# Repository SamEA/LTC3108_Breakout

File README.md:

LTC3108_Breakout
================

Energy Harvesting Breakout Board LTC3108

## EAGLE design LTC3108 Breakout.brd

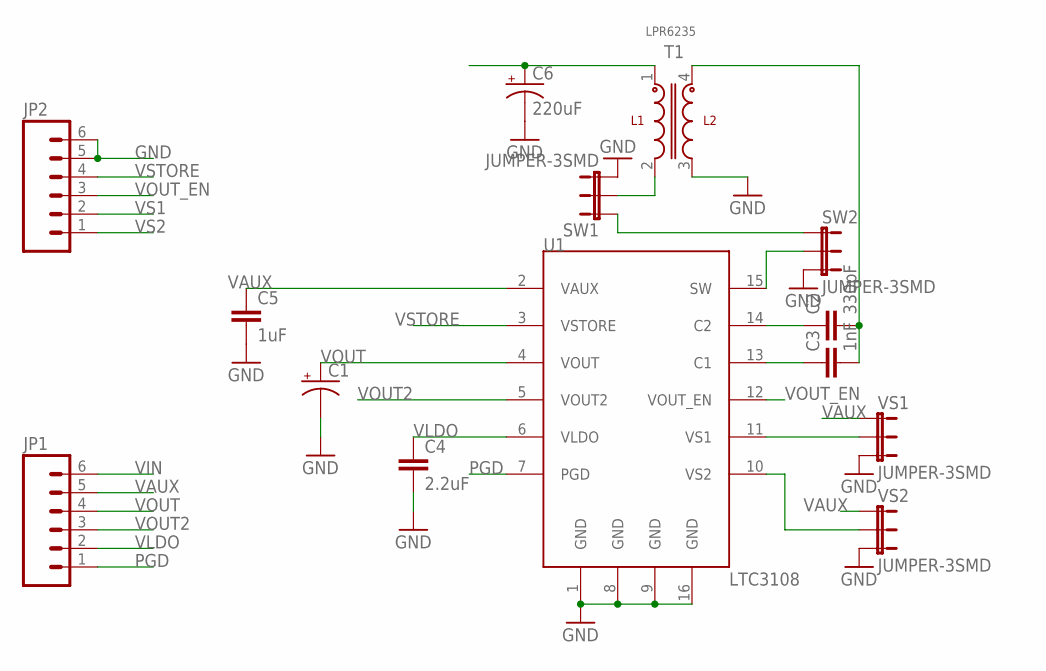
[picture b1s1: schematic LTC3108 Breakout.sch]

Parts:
C1: CAP_POL7343; EIA7343
C2: 330pF; 0603-CAP
C3: 1nF; 0603-CAP
C4: 2.2uF; 0603-CAP
C5: 1uF; 0603-CAP
C6: 220uF; EIA7343
JP1, JP2: M06SIP; 1X06
SW1, SW2: JUMPER-3SMD; SJ_3
T1: LPR6235
U1: LTC3108; SSOP
VS1, VS2: JUMPER-3SMD; SJ_3

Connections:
GND: C1.C (-), C4.2, C5.2, C6.C (-), JP2.5, JP2.6, SW1.3, SW2.3, T1.3, U1.1 (GND), U1.8 (GND), U1.9 (GND), U1.16 (GND), VS1.3, VS2.3
unnamed: C2.1, U1.14 (C2)
unnamed: C3.1, U1.13 (C1)
unnamed: C2.2, C3.2, T1.4
unnamed: SW2.2, U1.15 (SW)
unnamed: SW1.1, SW2.1
unnamed: SW1.2, T1.2
PGD: JP1.1, U1.7 (PGD)
VAUX: C5.1, JP1.5, U1.2 (VAUX), VS1.1, VS2.1
VIN: C6.A (+), JP1.6, T1.1
VLDO: C4.1, JP1.2, U1.6 (VLDO)
VOUT: C1.A (+), JP1.4, U1.4 (VOUT)
VOUT2: JP1.3, U1.5 (VOUT2)
VOUT_EN: JP2.3, U1.12 (VOUT_EN)
VS1: JP2.2, U1.11 (VS1), VS1.2
VS2: JP2.1, U1.10 (VS2), VS2.2
VSTORE: JP2.4, U1.3 (VSTORE)

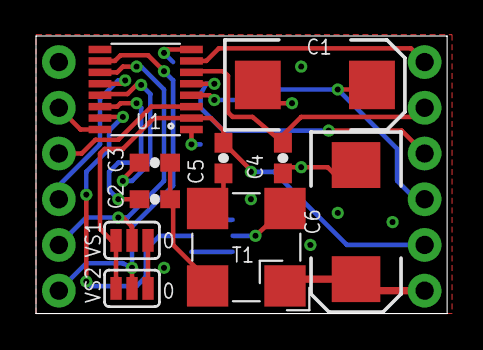
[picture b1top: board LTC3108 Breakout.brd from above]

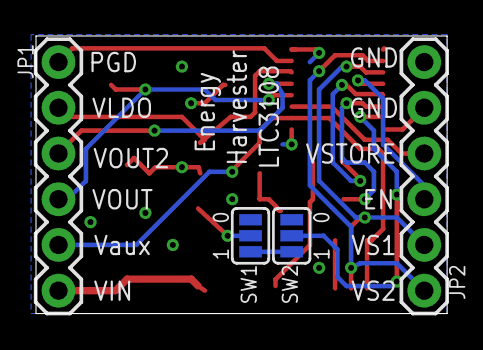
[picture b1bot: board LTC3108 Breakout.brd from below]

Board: 2 copper layers, 22.8 x 15.4 mm, 14 parts (4 on the bottom side), 17 nets.

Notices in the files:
parts and their libraries:
SparkFun-Passives: Licensing: CC v3.0 Share-Alike You are welcome to use this library for commercial purposes.
